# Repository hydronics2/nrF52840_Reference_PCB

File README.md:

# nrF52840_reference_PCB

This is a reference design for the nrF52840 for easy SWD programming and testing.  This layout uses the nrF52840 module from Raytek called the [MDBT50Q](http://www.raytac.com/upload/download_files/1bca545683ea4caf48e1ec796c09b9d9.pdf).
This PCB has been tested and it works!  This design relied heavily on the work of [Adafruit's feather board](https://www.adafruit.com/product/4062). I accidently ordered the -P1M version (PCB antenna). I think the -1M version chip antenna has slightly better range/performance.

I'm building an introduction class where I'd like to introduce students to soldering class, circuit python, and Internet of Things (IOT).  This module is also going to be a favorite for conference badges. This reference board is a good start. The changes from the feather are:
- broke out more pins
- changed the FLASH to an SOIC package
- changed some other packages slightly for easier soldering

You can order boards from Oshpark using this link: [project](https://oshpark.com/shared_projects/A5jKStz9).  

This board has been tested and it works!! 

Here's a list of parts:

- MDBT50Q-P1M (PCB Antenna) from [digikey](https://www.digikey.com/product-detail/en/seeed-technology-co-ltd/113990583/1597-1679-ND/9697026). 
 or the MDBT50Q-1M (chip Antenna) from [digikey](https://www.digikey.com/product-detail/en/seeed-technology-co-ltd/113990584/1597-1680-ND/9697027)
- QUAD SPI Flash 2MB [digikey](https://www.digikey.com/product-detail/en/gigadevice-semiconductor-hk-limited/GD25Q16CTIGR/1970-1010-1-ND/9484760)
- 10 pin SWD Header from [digikey](https://www.digikey.com/product-detail/en/microchip-technology/ATSAMD21E15L-AFT/1611-ATSAMD21E15L-AFTCT-ND/6832779)
- 	Inductor 10UH  [digikey](https://www.digikey.com/product-detail/en/taiyo-yuden/LBR2012T100K/587-2045-1-ND/1788992)
- 3.3V Regulator (18V max input) [mouser](https://www.mouser.com/ProductDetail/511-LDL1117S50R)

- USB micro connector [digikey](https://www.digikey.com/product-detail/en/amphenol-icc-fci/10118194-0001LF/609-4618-1-ND/2785382)
- standard 6mmx6mm tactile RESET button [sparkfun](https://www.sparkfun.com/products/97)
- screw terminal 5mm pitch [sparkfun](https://www.sparkfun.com/products/8432) or [aliexpress](https://www.aliexpress.com/wholesale?catId=0&initiative_id=SB_20190221221755&SearchText=pcb+screw+terminal)
- input protection diodes on the 12V and USB input into the regulator. This is Adafruit's design. [digikey](https://www.digikey.com/product-detail/en/diodes-incorporated/B130-13-F/B130-FDICT-ND/815318)
- 32.768khz crystal (if needed, see above trinket design) [digikey](https://www.digikey.com/product-detail/en/epson/FC-135-32.7680KA-AG3/SER4086DKR-ND/6132726)
- crystal capacitors C7/C8 based on a 7pf load from the above crystal and assumed 2pf stray capacitence, CX1 = CX2 = 2(7pF - 2pF) = 10pF [digikey](https://www.digikey.com/product-detail/en/wurth-electronics-inc/885012006051/732-7793-1-ND/5454420)

SWD Programmer/Debugger: [Segger](https://www.digikey.com/product-detail/en/segger-microcontroller-systems/8.08.91-J-LINK-EDU-MINI/899-1061-ND/7387472)

Notes:
- need to add a ground plane
- circuit python requires additional storage in the form of SPI Flash storage to hold files and libraries. For an extra $0.60 you can double to size of your flash to 4MB. Might be worth trying.

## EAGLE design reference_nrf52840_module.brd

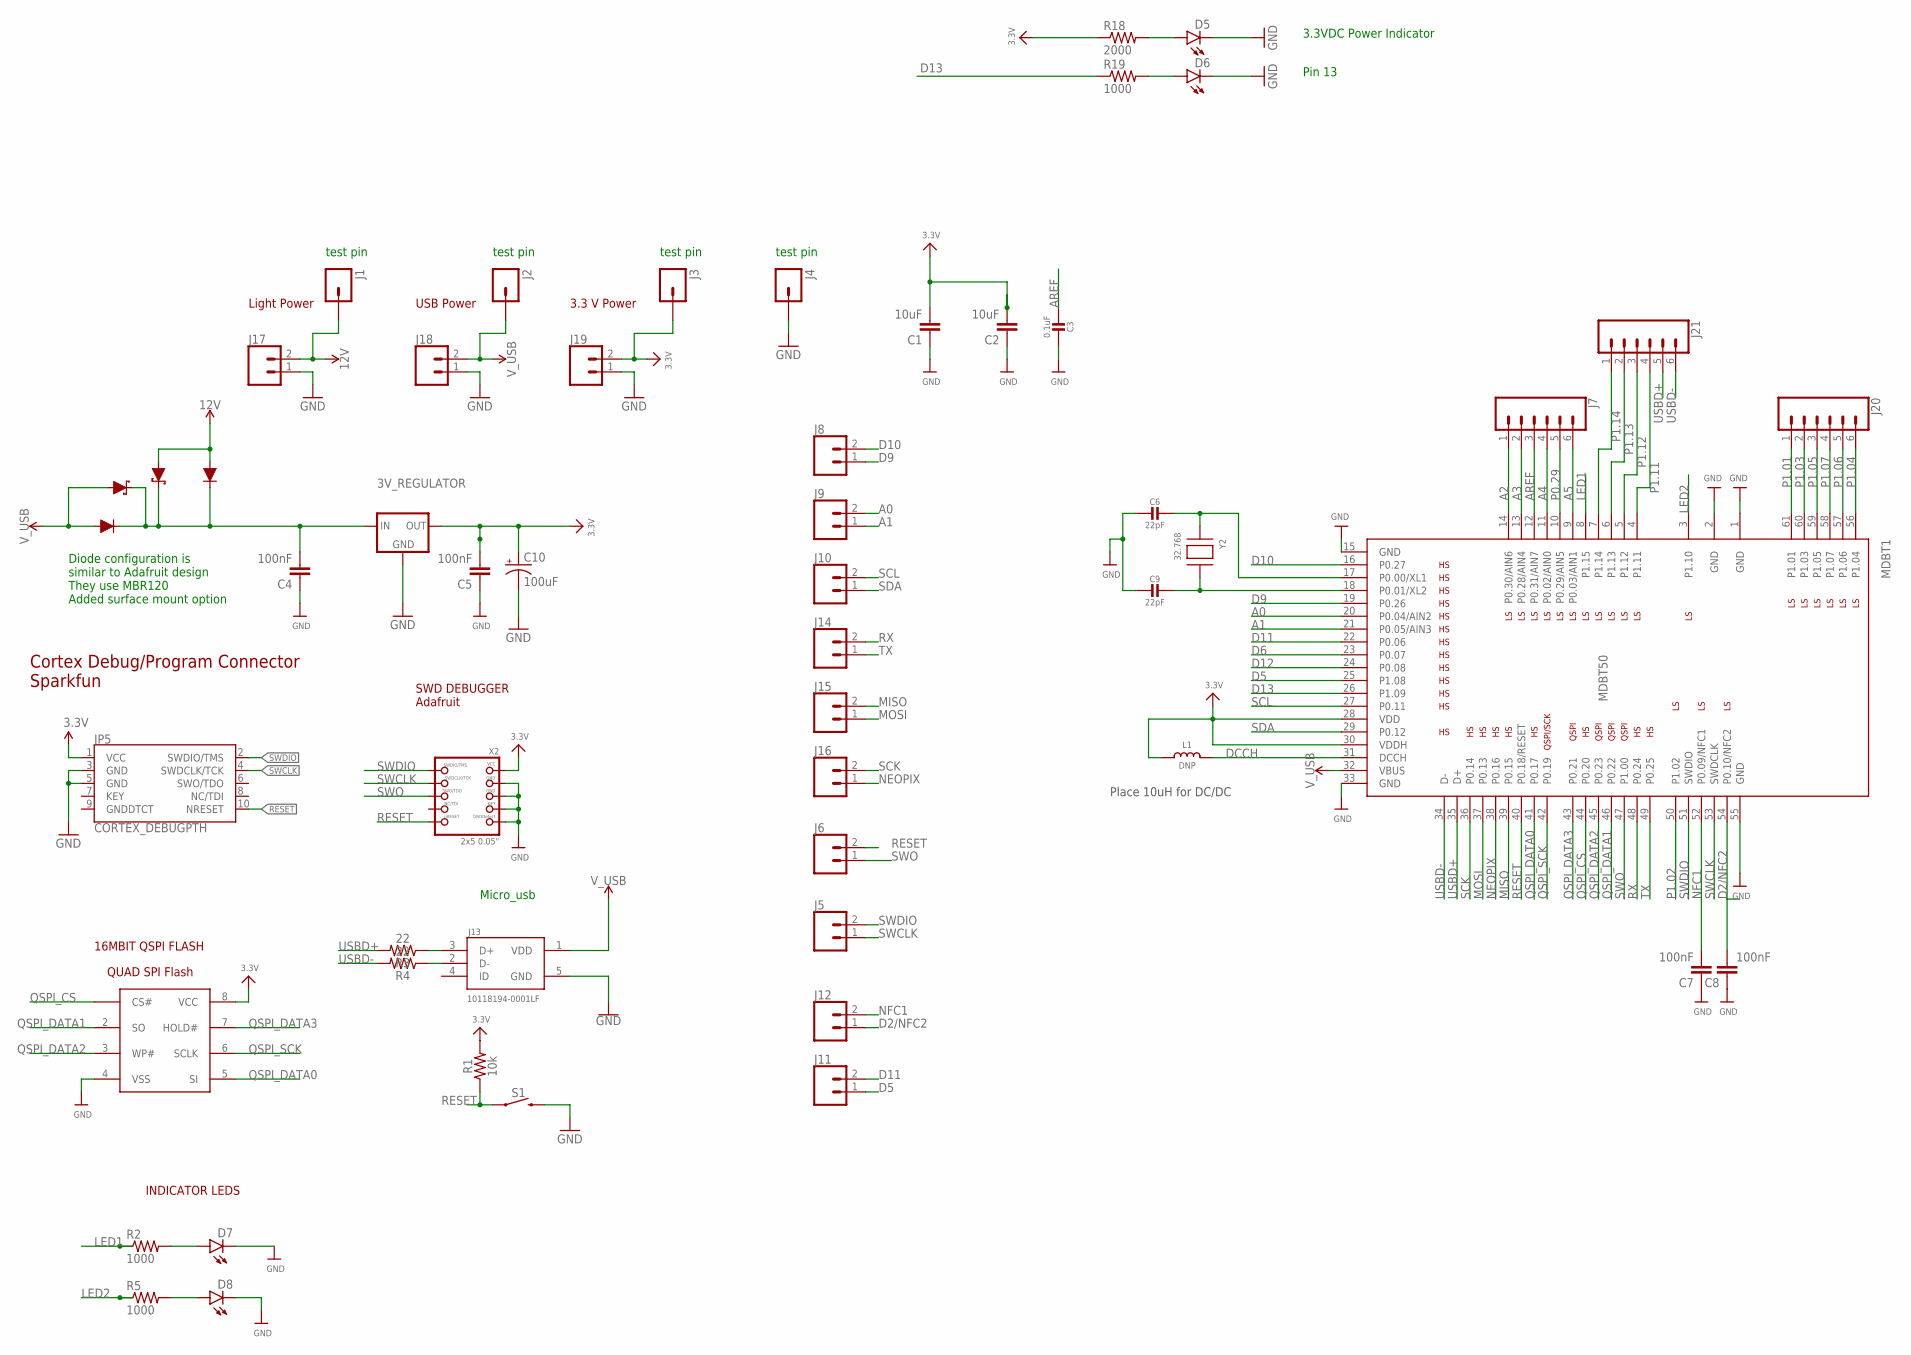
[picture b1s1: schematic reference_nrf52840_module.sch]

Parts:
3V_REGULATOR: LDL1117_5V_REG; SOT223
C1, C2: 10uF; 0805
C3: 0.1uF; _0805
C4, C5, C7, C8: 100nF; 0805
C6, C9: 22pF; 0603-NO
C10: 100uF; CPOL-RADIAL-2.5MM-6.5MM
D1, D2: 1A/50V/1.1V; DIODE-1N4001
D3, D4: 3A/40V/500mV; SMA-DIODE
D5, D6, D7, D8: LED1206; LED-1206
J1, J2, J3, J4: M01PTH; 1X01
J5, J6, J8, J9, J10, J11, J12, J14, J15, J16, J17, J18, J19: CONN_025MM; SCREWTERMINAL-5MM-2
J7, J20, J21: CONN_06NO_SILK_FEMALE_PTH; 1X06_NO_SILK
J13: 10118194-0001LF; FRAMATOME_10118194-0001LF
JP5: CORTEX_DEBUGPTH; 2X5-PTH-1.27MM
L1: DNP; _0805MP
MDBT1: MDBT50
R1: 10k; 0805
R2, R5, R19: 1000; 0805
R3, R4: 22; 0805
R18: 2000; 0805
S1: MOMENTARY-SWITCH-SPST-PTH-6.0MM-KIT; TACTILE_SWITCH_PTH_6.0MM_KIT
U$4: QUAD_SPI_FLASH; SO08
X2: 2x5 0.05"; 2X05_1.27MM_BOX_POSTS
Y2: 32.768; XTAL3215

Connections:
3.3V: 3V_REGULATOR.2 (OUT), 3V_REGULATOR.4 (OUT), C1.2, C2.2, C5.2, C10.1 (+), J3.1, J19.2, JP5.1 (VCC), L1.1, MDBT1.28 (VDD), MDBT1.30 (VDDH), R1.2, R18.1, U$4.8 (VCC), X2.1 (VCC)
12V: D1.A, D3.A, J1.1, J17.2
A0: J9.2, MDBT1.20 (P0.04/AIN2)
A1: J9.1, MDBT1.21 (P0.05/AIN3)
A2: J7.1, MDBT1.14 (P0.30/AIN6)
A3: J7.2, MDBT1.13 (P0.28/AIN4)
A4: J7.4, MDBT1.11 (P0.02/AIN0)
A5: J7.6, MDBT1.9 (P0.03/AIN1)
AREF: C3.2, J7.3, MDBT1.12 (P0.31/AIN7)
D2/NFC2: C8.2, J12.1, MDBT1.54 (P0.10/NFC2)
D5: J11.1, MDBT1.25 (P1.08)
D6: MDBT1.23 (P0.07)
D9: J8.1, MDBT1.19 (P0.26)
D10: J8.2, MDBT1.16 (P0.27)
D11: J11.2, MDBT1.22 (P0.06)
D12: MDBT1.24 (P0.08)
D13: MDBT1.26 (P1.09), R19.1
DCCH: L1.2, MDBT1.31 (DCCH)
GND: 3V_REGULATOR.1 (GND), C1.1, C2.1, C3.1, C4.1, C5.1, C6.2, C7.1, C8.1, C9.2, C10.2 (-), D5.C, D6.C, D7.C, D8.C, J4.1, J13.5 (GND), J17.1, J18.1, J19.1, JP5.3 (GND), JP5.5 (GND), MDBT1.1 (GND), MDBT1.2 (GND), MDBT1.15 (GND), MDBT1.33 (GND), MDBT1.55 (GND), S1.3 (2), U$4.4 (VSS), X2.3 (GND), X2.5 (GND), X2.7 (KEY), X2.9 (GNDDETECT)
LED1: MDBT1.8 (P1.15), R2.1
LED2: MDBT1.3 (P1.10), R5.1
MISO: J15.2, MDBT1.39 (P0.15)
MOSI: J15.1, MDBT1.37 (P0.13)
unnamed: D7.A, R2.2
unnamed: J13.3 (D+), R3.1
unnamed: J13.2 (D-), R4.1
unnamed: 3V_REGULATOR.3 (IN), C4.2, D1.C, D2.C, D3.C, D4.C
unnamed: C9.1, MDBT1.18 (P0.01/XL2), Y2.P$2
unnamed: C6.1, MDBT1.17 (P0.00/XL1), Y2.P$1
unnamed: D8.A, R5.2
unnamed: D5.A, R18.2
unnamed: D6.A, R19.2
NEOPIX: J16.1, MDBT1.38 (P0.16)
NFC1: C7.2, J12.2, MDBT1.52 (P0.09/NFC1)
P0.29: J7.5, MDBT1.10 (P0.29/AIN5)
P1.01: J20.1, MDBT1.61 (P1.01)
P1.02: MDBT1.50 (P1.02)
P1.03: J20.2, MDBT1.60 (P1.03)
P1.04: J20.6, MDBT1.56 (P1.04)
P1.05: J20.3, MDBT1.59 (P1.05)
P1.06: J20.5, MDBT1.57 (P1.06)
P1.07: J20.4, MDBT1.58 (P1.07)
P1.11: J21.4, MDBT1.4 (P1.11)
P1.12: J21.3, MDBT1.5 (P1.12)
P1.13: J21.2, MDBT1.6 (P1.13)
P1.14: J21.1, MDBT1.7 (P1.14)
QSPI_CS: MDBT1.44 (P0.20), U$4.1 (CS#)
QSPI_DATA0: MDBT1.41 (P0.17), U$4.5 (SI)
QSPI_DATA1: MDBT1.46 (P0.22), U$4.2 (SO)
QSPI_DATA2: MDBT1.45 (P0.23), U$4.3 (WP#)
QSPI_DATA3: MDBT1.43 (P0.21), U$4.7 (HOLD#)
QSPI_SCK: MDBT1.42 (P0.19), U$4.6 (SCLK)
RESET: J6.2, JP5.10 (NRESET), MDBT1.40 (P0.18/RESET), R1.1, S1.1, X2.10 (NRESET)
RX: J14.2, MDBT1.48 (P0.24)
SCK: J16.2, MDBT1.36 (P0.14)
SCL: J10.2, MDBT1.27 (P0.11)
SDA: J10.1, MDBT1.29 (P0.12)
SWCLK: J5.1, JP5.4 (SWDCLK/TCK), MDBT1.53 (SWDCLK), X2.4 (SWDCLK)
SWDIO: J5.2, JP5.2 (SWDIO/TMS), MDBT1.51 (SWDIO), X2.2 (SWDIO)
SWO: J6.1, MDBT1.47 (P1.00), X2.6 (SWO)
TX: J14.1, MDBT1.49 (P0.25)
USBD+: J21.5, MDBT1.35 (D+), R3.2
USBD-: J21.6, MDBT1.34 (D-), R4.2
V_USB: D2.A, D4.A, J2.1, J13.1 (VDD), J18.2, MDBT1.32 (VBUS)

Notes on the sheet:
SWD DEBUGGER Adafruit
Cortex Debug/Program Connector Sparkfun
Micro_usb
Light Power
USB Power
3.3 V Power
Diode configuration is similar to Adafruit design They use MBR120 Added surface mount option
3.3VDC Power Indicator
Pin 13
test pin
Place 10uH for DC/DC
16MBIT QSPI FLASH
INDICATOR LEDS

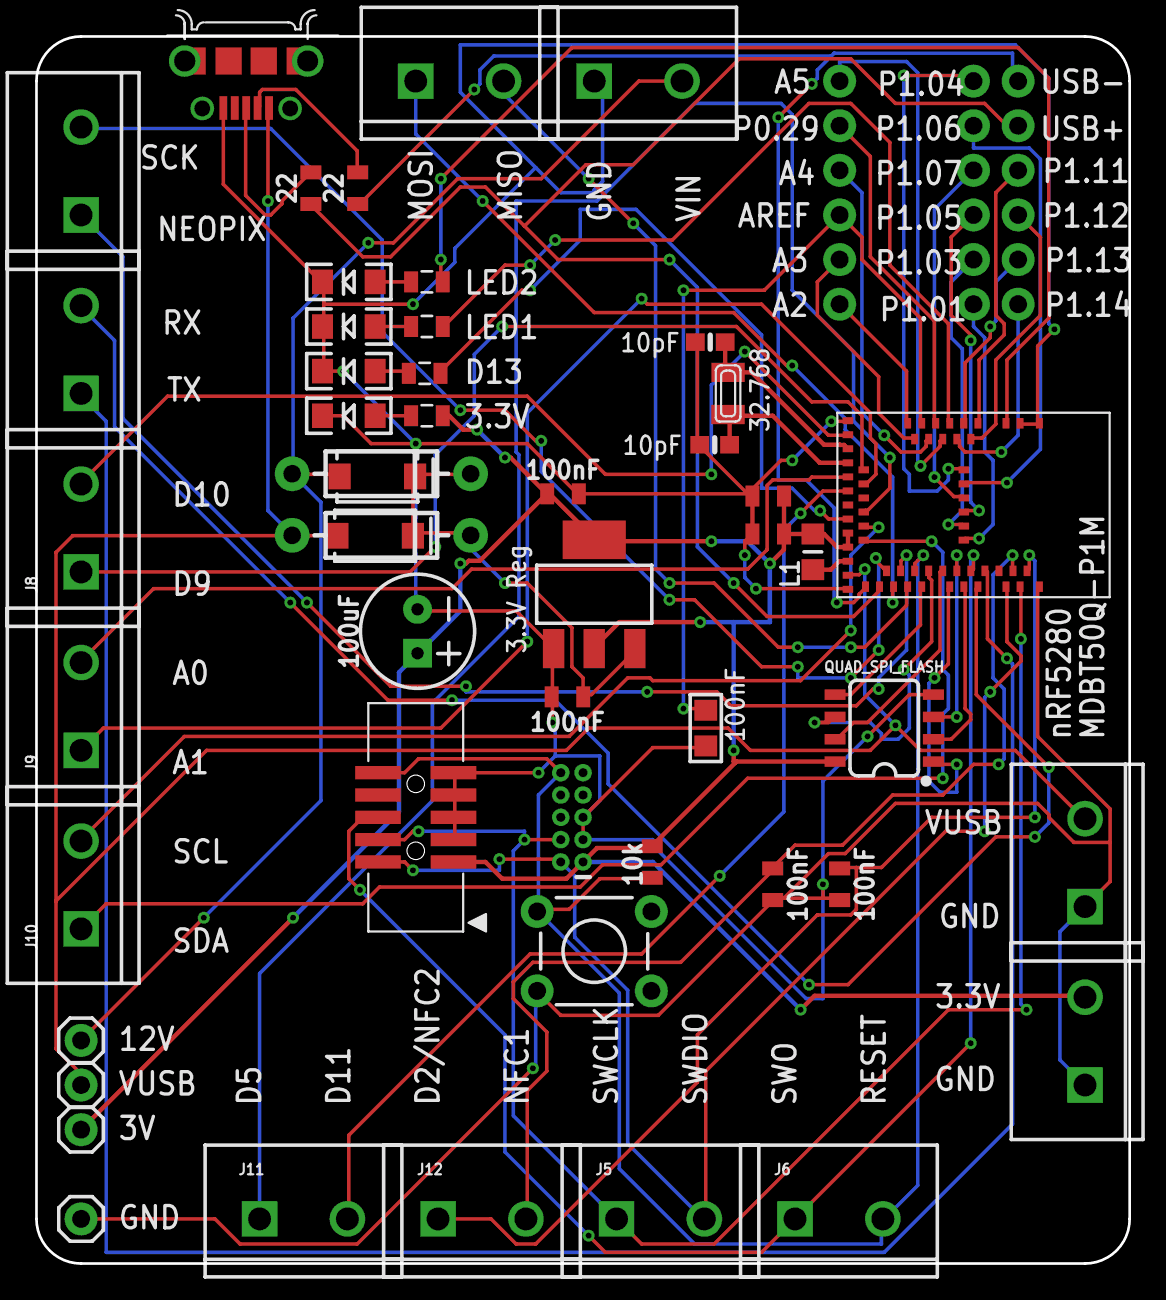
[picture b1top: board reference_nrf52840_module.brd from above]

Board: 2 copper layers, 62.2 x 69.9 mm, 54 parts (0 on the bottom side), 61 nets.

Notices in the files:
parts and their libraries:
microbuilder: This work is placed in the public domain, and may be freely used for commercial and non-commercial work with the following conditions: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
SparkFun-Resistors: Licensing: Creative Commons ShareAlike 4.0 International - https://creativecommons.org/licenses/by-sa/4.0
